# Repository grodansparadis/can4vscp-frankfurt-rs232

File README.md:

# Frankfurt RS-232

## Abstract

Frankfurt RS-232 interfaces serial RS-232 to the CAN4VSCP bus and is powered from the CAN4VSCP bus. It can be used with a USB to serial adapter free of charge so it can also be connected to host computers that does not have a RS-232 port. The Frankfurt RS-232 is designed to be mounted on a DIN rail or screwed on to a wall or used in an other installed fashion. This module is as our other modules designed to do its work behind the scenes. It is a powerful and reliable workhorse that does not need to be in the centre of the spotlights to do the work it is designed for.

It is important to note that Frankfurt RS-232 is not a general CAN interface. The CAN speed of the device is fixed to 125 kbps and the serial speed is fixed at 115200 baud 8N1. This is because the Frankfurt RS-232 is made for the CAN4VSCP bus and VSCP and therefore does not need the variable speeds. If you need a general CAN adapter please look at [Rusoku Technologies TouCan](https://www.rusoku.com/products) or other CAN <-> USB interfaces.

Frankfurt RS-232 have three working modes:

## Verbose mode
In this mode easy to remember and use text based commands can be issued to control the device. It is possible to find VSCP nodes on the connected CAN4VSCP bus, read and write registers and many other of the common functions needed to diagnose a CAN4VSCP system. The mode is created for users that need to check up on a CAN4VSCP network and get diagnostic information etc. It is possible to go to this mode from any of the other modes at any time and therefore get the most out of each modes available functionality.

## CAN4VSCP mode
This mode uses the efficient and secure VSCP serial protocol to talk to a host computer. Drivers for Windows and Linux is readably available and it is a turn key solution to connect any CAN4VSCP bus to a host. The driver follows the CANAL standard so both the VSCP Daemon and the VSCP Works programs can be used.

## SLCAN mode
The Swedish company Lawicel AB and Lars Wictorsson created a serial protocol for CAN adapters that since been a standard for such devices. The SLCAN mode of Frankfurt RS-232 support a limited set of commands from this standard so that the module can be connected to the Socketcan system available for Linux. Se the manual for the commands that are implemented. Also in this case the CAN speed is fixed at 125 kbps and the serial speed is fixed at 115200 kbps.

It is possible to have hundreds of Frankfurt RS-232 modules connected to a host computer where each in turn is connected to hundreds of nodes, thereby building very large and complex systems. Together with cards like Raspberry Pi, Beaglebone and others it is possible to have distributed control systems controlled over Ethernet and TCP/IP. 

<hr>

## Project files

### User manual
  * [User Manual](https://grodansparadis.github.io/can4vscp-frankfurt-rs232/#)

### Schematic, PCB, 3D files etc
  * [Schematics reversion B](docs/images/schema_rev_B.png)
 * Hardware design files is made in [KiCad](https://kicad.org) and can be found in the `kicad` directory. Valid from reversion C of the hardware.
   * Gerber files for PCB production can be found in the `gerber` directory (in the `kicad` folder).
 * Eagle schema and board files for reversion A, B and B can be found in the `eagle` directory. Only the KiCad version is actively updated.

 ### Firmware

 The firmware is developed in [MPLAB X IDE](https://www.microchip.com/mplab/mplab-x-ide) using the [XC8 compiler](https://www.microchip.com/mplab/compilers).

  * Binary release files is available [here](https://github.com/grodansparadis/can4vscp-frankfurt-rs232/releases)

### MDF - Module Description File(s)
No MDF is available for this module.

### Support
If you need support, please open an issue in the [GitHub repository](https://github.com/grodansparadis/can4vscp-frankfurt-rs232/issues).

### Buy a ready made modules
You can buy a ready made module from [Grodans Paradis](http://www.grodansparadis.com).

### Project related links
  * [VSCP project](https://www.vscp.org)
  * [VSCP Documentation site](https://docs.vscp.org/)
  * [VSCP Wiki](https://github.com/grodansparadis/vscp/wiki)

<hr>

This project is part of the <a href="http://www.vscp.org">VSCP (Very Simple Control Protocol) project</a>. 

<hr>

This project is licensed under the 
<a href="http://creativecommons.org/licenses/by-nc-sa/3.0/">Creative Commons open source license Attribution-NonCommercial-ShareAlike 3.0 Unported</a>. 
Other license options are available by conacting <a href="malto:info@grodansparadis.com">Paradis of the Frog AB</a>

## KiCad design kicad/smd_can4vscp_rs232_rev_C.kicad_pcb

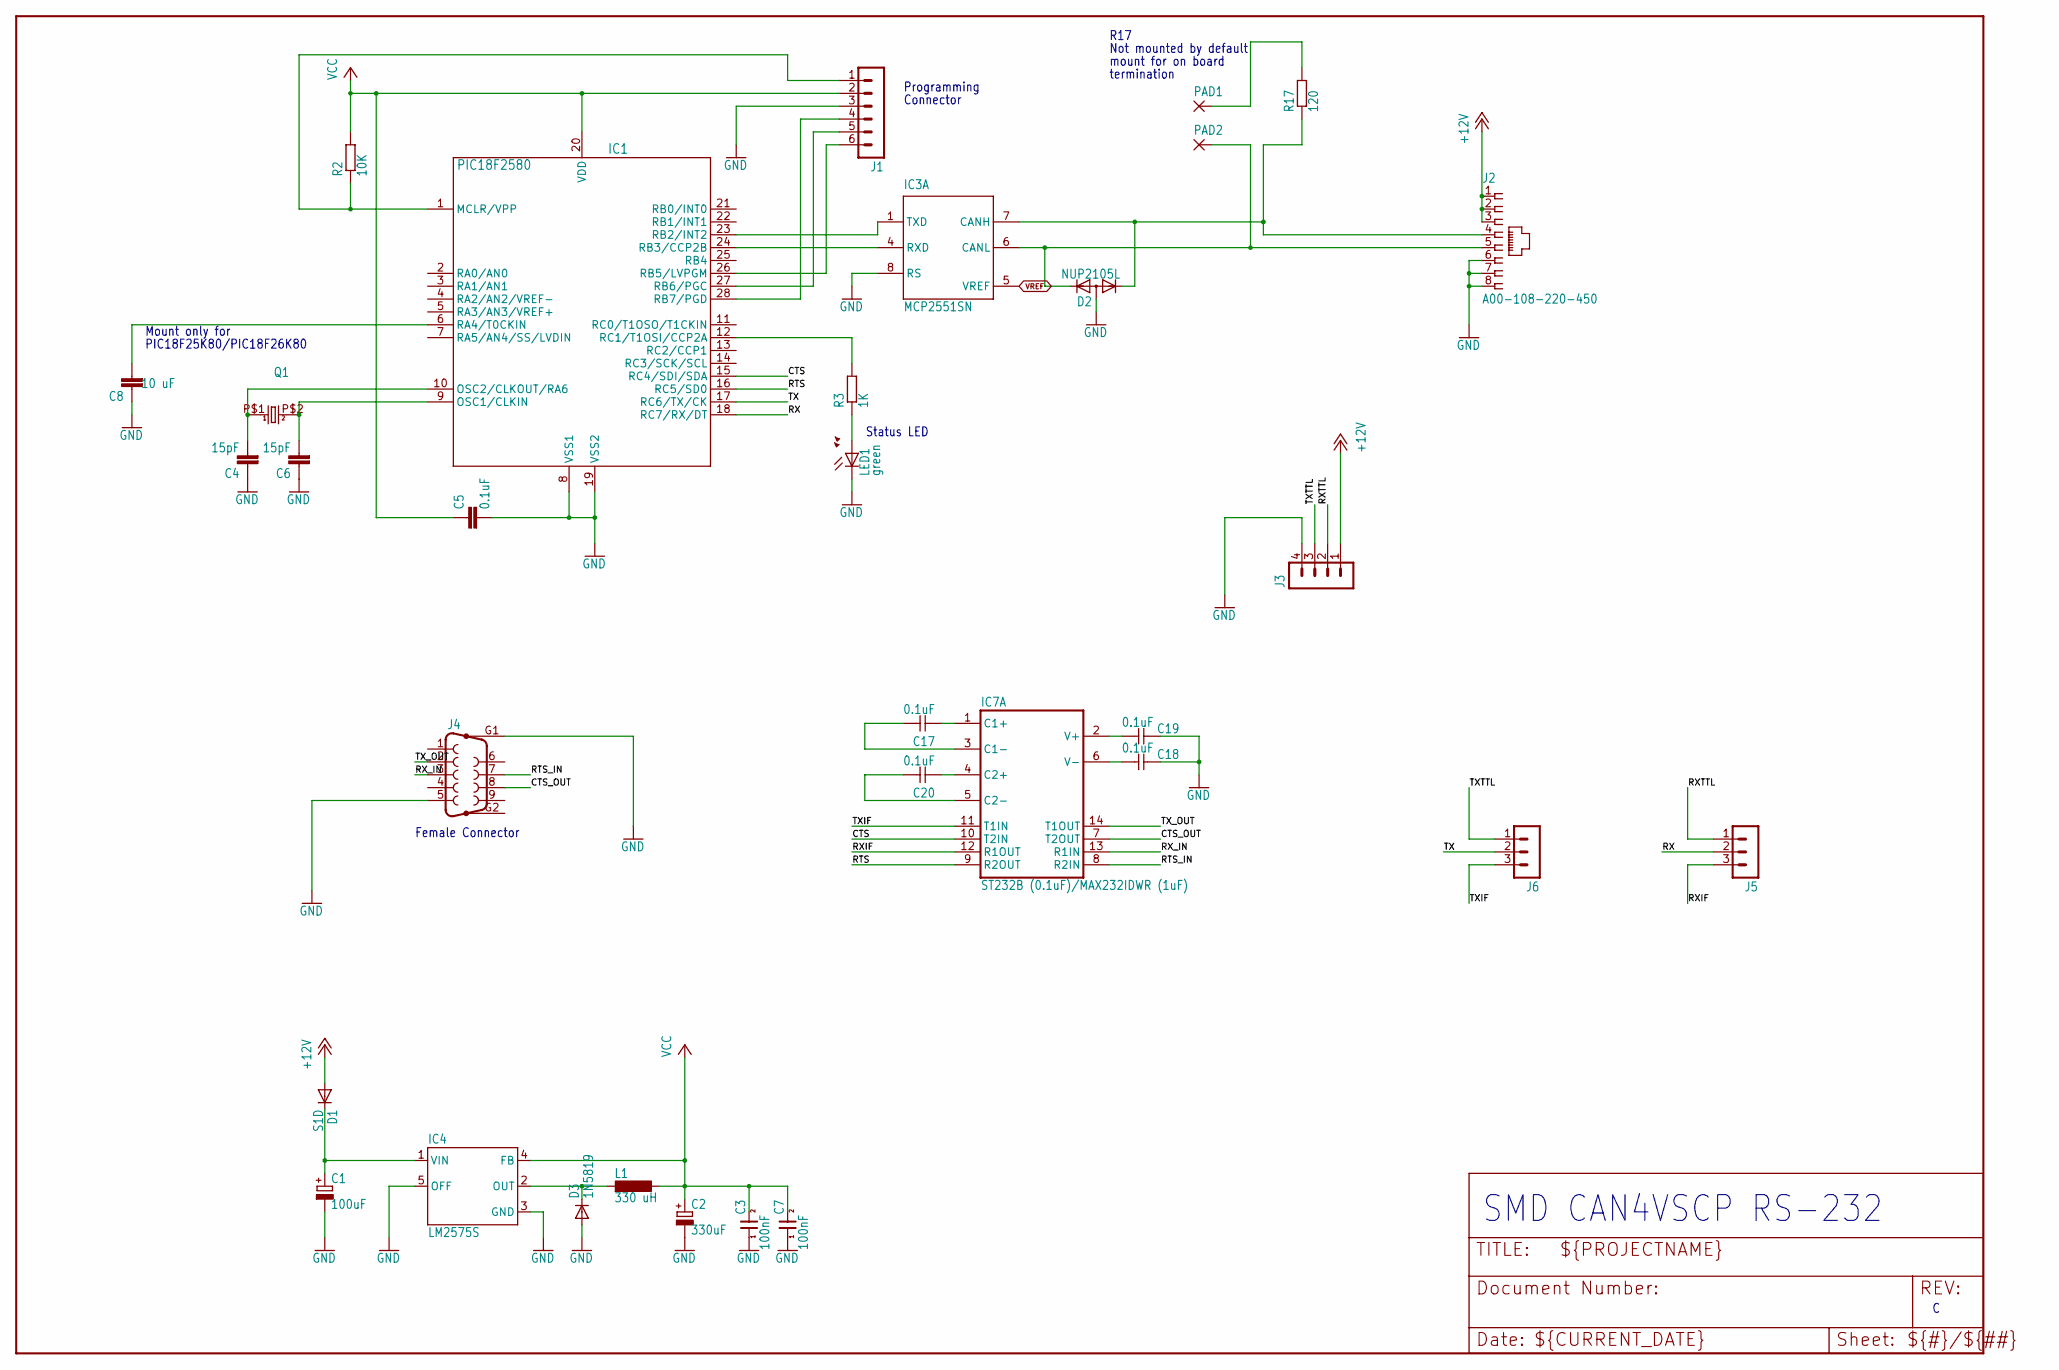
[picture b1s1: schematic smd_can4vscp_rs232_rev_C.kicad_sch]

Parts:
C1: 100uF; PANASONIC_D
C2: 330uF; PANASONIC_D
C3, C7: 100nF; 0805
C4, C6: 15pF; C0805
C5, C17, C18, C19, C20: 0.1uF; C0805
C8: 10 uF; C0805
D1: S1D; SOD123
D2: NUP2105L; SOT23
D3: 1N5819; SOD123
IC1: PIC18F2580; SO28
IC3: MCP2551SN; SO-08
IC4: LM2575S; TO263-5
IC7: ST232B (0.1uF)/MAX232IDWR (1uF); SO16L
J1: MA06-1
J2: A00-108-220-450; RJ-45
J3: MA04-1
J4: F09HP
J5, J6: MA03-1
L1: 330 uH; DO3316P
LED1: green; CHIPLED_0805
PAD1, PAD2: 1,6/0,8; 1,6_0,8
Q1: HC-49S; 9C
R2: 10K; R0805
R3: 1K; R0805
R17: 120; R0805

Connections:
+12V: D1.A, J2.1, J2.2, J2.3, J3.1
CANL1: D2.1 (K1), IC3.7 (CANH), J2.4, R17.1
CTS: IC1.15 (RC4/SDI/SDA), IC7.10 (T2IN)
CTS_OUT: IC7.7 (T2OUT), J4.8
GND: C1.-, C2.-, C3.1, C4.1, C5.2, C6.1, C7.1, C8.1, C18.1, C19.1, D2.3 (A), D3.A, IC1.8 (VSS1), IC1.19 (VSS2), IC3.2 (VSS), IC3.8 (RS), IC4.3 (GND), IC4.5 (OFF), IC7.15 (GND), J1.3, J2.6, J2.7, J2.8, J3.4, J4.5, J4.G1, LED1.C
unnamed: D3.C, IC4.2 (OUT), L1.1
unnamed: C4.2, IC1.10 (OSC2/CLKOUT/RA6), Q1.P$1 (1)
unnamed: C1.+, D1.C, IC4.1 (VIN)
unnamed: IC1.12 (RC1/T1OSI/CCP2A), R3.2
unnamed: LED1.A, R3.1
unnamed: D2.2 (K2), IC3.6 (CANL), J2.5, PAD2.1
unnamed: C6.2, IC1.9 (OSC1/CLKIN), Q1.P$2 (2)
unnamed: PAD1.1, R17.2
unnamed: IC7.11 (T1IN), J6.3
unnamed: IC1.1 (MCLR/VPP), J1.1, R2.1
unnamed: IC1.28 (RB7/PGD), J1.4
unnamed: IC1.27 (RB6/PGC), J1.5
unnamed: IC1.26 (RB5/LVPGM), J1.6
unnamed: C17.1, IC7.1 (C1+)
unnamed: C17.2, IC7.3 (C1-)
unnamed: C20.1, IC7.4 (C2+)
unnamed: C20.2, IC7.5 (C2-)
unnamed: C19.2, IC7.2 (V+)
unnamed: C18.2, IC7.6 (V-)
RTS: IC1.16 (RC5/SD0), IC7.9 (R2OUT)
RTS_IN: IC7.8 (R2IN), J4.7
RX: IC1.18 (RC7/RX/DT), J5.2
RXCAN: IC1.24 (RB3/CCP2B), IC3.4 (RXD)
RXIF: J3.3, J6.1
RXTTL: C8.2, IC1.6 (RA4/T0CKIN)
RX_IN: IC7.13 (R1IN), J4.3
TX: IC1.17 (RC6/TX/CK), J6.2
TXCAN: IC1.23 (RB2/INT2), IC3.1 (TXD)
TXIF: IC7.12 (R1OUT), J5.3
TXTTL: J3.2, J5.1
TX_OUT: IC7.14 (T1OUT), J4.2
VCC: C2.+, C3.2, C5.1, C7.2, IC1.20 (VDD), IC3.3 (VDD), IC4.4 (FB), IC7.16 (VCC), J1.2, L1.2, R2.2
VREF: IC3.5 (VREF)

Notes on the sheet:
Mount only for
Status LED
Female Connector
Not mounted by default
termination
PIC18F25K80/PIC18F26K80
Connector
mount for on board
R17
Programming
SMD CAN4VSCP RS-232

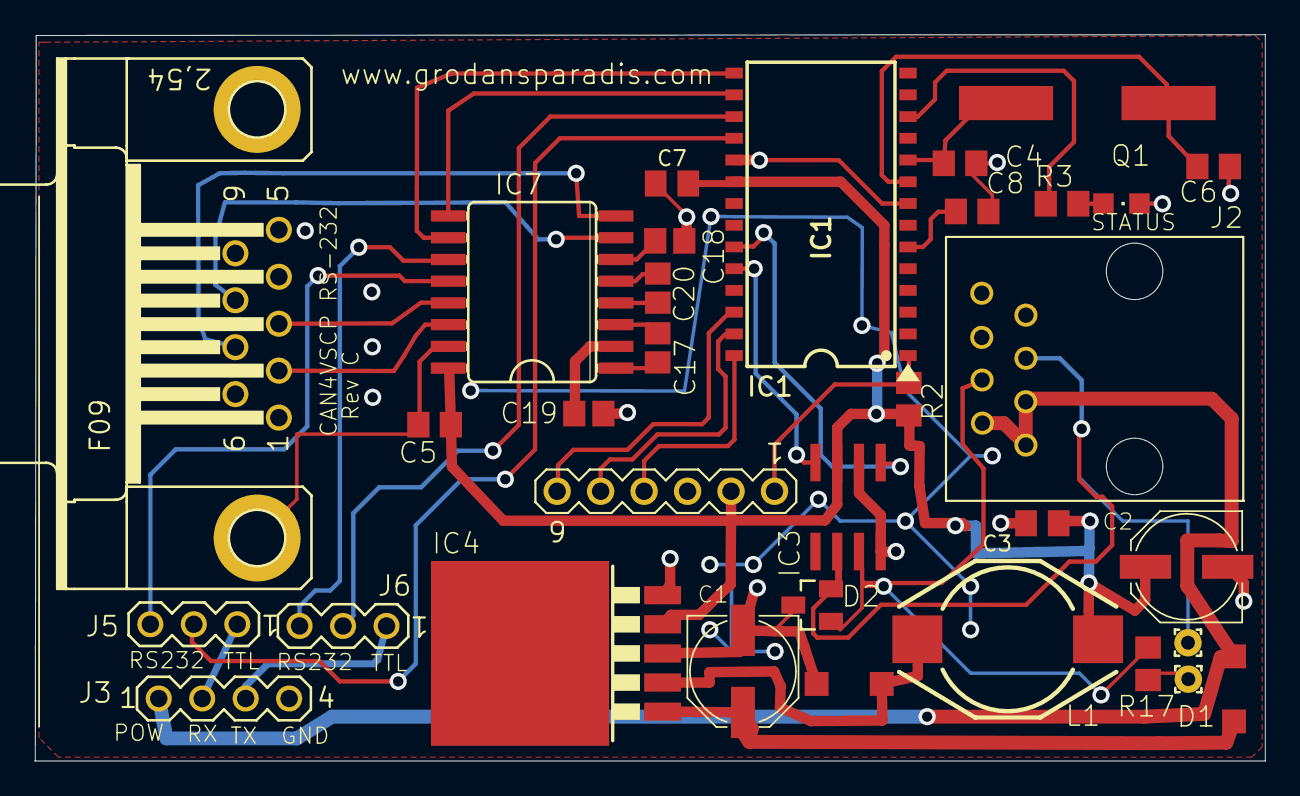
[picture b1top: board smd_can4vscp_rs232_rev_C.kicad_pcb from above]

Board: 6 copper layers, 71.9 x 42.4 mm, 33 parts (0 on the bottom side), 37 nets.

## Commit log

2015-02-13 Moved from hardware repository
2015-02-14 Renamed
2015-02-14 Removed unused folder
2015-02-24 Added interrupt driver CAN receive
2015-02-24 Coding multiframe
2015-02-26 Wordk and tested in single frame
2015-03-01 Added the rest if the folder for the project
2015-03-02 Added switches for RS-232/TTL
2015-03-13 All verbose commands now return +OK
2015-03-16 Added serial bootloader
2015-03-17 Updated bootloader. Works now
2015-03-24 First release
2015-03-24 Added release firmware folders
2015-03-24 Distro files
2015-04-20 Removed VCC from VCAP.
2015-06-15 Moved the old hygrogen project
2015-06-24 Using peripheral eeprom functions now
2015-07-27 Fixed problem with send timeout
2015-08-17 Changed license to Artistic License 3.0
2015-09-27 Added task
2015-10-02 Fixed buffer overflow
2015-10-05 Solved problem where a buffer overun resulting in a bad crc sent nonsense out on the CAN bus.
2015-10-05 Fixed #5
2015-10-05 Fixes #3
2015-10-06 Added set defaults command that set all persistent values to there default value.
2015-10-06 Fixes #1
2015-10-06 Fixes #2
2015-10-07 Fixed #6
2015-10-07 Timestamp now works in verbose mode
2015-10-08 Baudrates
2015-10-09 Everything in place so ready (maybe) for release.
2015-11-13 Added firmware readme
2015-11-15 Prepareing for 1.1.0 release
2015-11-15 Added the binaries for 1.1.0
2015-11-23 Prepare versin 1.1.1
2015-11-23 Prepare for version 1.1.1
2015-11-25 Bus warning blink was never turned off. Fixed.
2015-11-26 Prepare for 1.1.2
2015-11-26 Moved the history file to the root folder
2015-11-26 Edit
2015-12-17 Updated readme and license
2015-12-17 Changed copyright info in headers so it is correct
2015-12-22 Added ignores
2016-03-08 Adopted for PIC18F26K80.
2016-03-08 Updated copyright info
2016-03-23 Fixed environment
2016-04-19 RA4 set to input to prevent collision with VCAP circuits in PIC18F2580. Brown out raised to maximum (3V & 4.6V). Valuable input from Anders Forsgren, AJE Electronics AB.
2016-05-04 Changed bit time calculation link
2018-09-08 Changed copyright year
2019-10-08 Fixed path changes that caused a show stopper
2019-10-08 Fixed uart char write error
2019-10-08 Added an image folder
2019-10-09 Fixed problem that prevented mode switching when in VSCP serial protocol mode.
2019-10-09 Updated instructions in firmware folder
2019-12-09 Fixed path to firmware file that changed earlier in history
2020-05-08 Added image for group 'dialout' permission
2020-05-15 Updated copyright dates
2021-09-06 Moved wiki to docs for firther processing
2021-09-06 Updated project files
2025-02-07 Added raw copy for future manual update
2025-09-23 Renamed files for new naming convention
2025-09-24 Converted schema to kicad
2025-09-24 Removed old hydrogen project
2025-09-24 Updated README to look like for other modules
2025-09-25 Moved inages to docs folder
2025-09-25 Updated docs to Markdown (docisfy)
2025-09-25 Fixed links to changed URL's
2025-09-29 Fixed link to docs and release files
2025-09-29 Chamhed link to schema
2025-09-29 Driver links
2025-09-29 Fixed link to manual
2025-09-29 Fixed link to latest schema
2025-09-29 Fixed broken links
2025-09-29 Cleaning up
2025-09-30 /home/akhe/development/VSCP/can4vscp-odessa/LICENSE
2025-09-30 Fixed link to issues
2025-10-01 Clean up
2025-10-01 Added pictures from the website
2026-05-05 Updated license to CERN
